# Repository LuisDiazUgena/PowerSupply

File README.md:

#BreadBoard Power Supply

Works with center positive DC supply.

Uses L7805 module and capacitors to smooth signal. Maybe you need to attach a power sink to it.

**(Avoid to touch it, anyway)**

###PCB

I've milled the board, but I'm sure it will work with PCB Insulation too.

You will find schematics, pcb design files, gerbers and gcode inside PCB folder.

I've milled with a 60 degrees V drill (deep=0.15mm/diameter=0,52mm).

##Pictures

* Before soldering:

* After soldering:

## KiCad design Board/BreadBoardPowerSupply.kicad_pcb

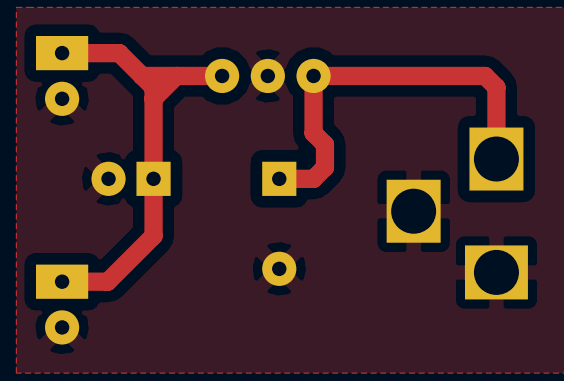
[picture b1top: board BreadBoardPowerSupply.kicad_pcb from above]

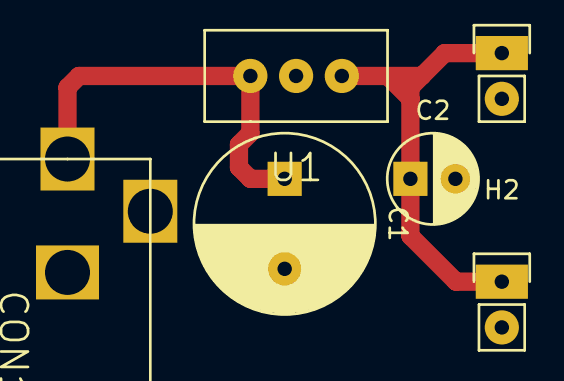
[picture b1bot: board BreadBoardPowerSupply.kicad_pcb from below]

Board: 2 copper layers, 6 parts (6 on the bottom side), 3 nets.

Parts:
C1: CP; C_Radial_D10_L13_P5
C2: CP; C_Radial_D5_L6_P2.5
CON1: BARREL_JACK
H1, H2: Header_1x02; Pin_Header_Straight_1x02
U1: 7805; LM7805

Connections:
5V: C2.1, H1.1, H2.1, U1.VO
GND: C1.2, C2.2, CON1.2, CON1.3, H1.2, H2.2, U1.GND
unnamed: C1.1, CON1.1, U1.VI

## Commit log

2015-08-17 Added eschematich, pcb layout, gerbers and gcode to drill it
2015-08-17 Added info about the project
2015-08-17 Added image of pcb layout
2015-08-18 Added before/after soldering pics
2015-08-18 Added info about pcb milling and pictures
2015-08-24 Update schematics (added polarised capacitors)
